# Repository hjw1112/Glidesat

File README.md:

# Glidesat
Custom devboard with additional components for ESA cansat competition. 

This PCB is for ESA cansat competition and I made it because I thought premade devboards like rp pico is too big and limiting for my team's goal. So I made this devboard to save as much space as possible and to connect to CM4 module for image processing. 

It is most complex PCB project so it was quite difficult to work on it, but with some help from background knowledge from previous projects, i think it went smoothly :)

Here are screenshots of PCB Design

## PCB Design

## Schematic

## 3D View

## Soldered PCB

---

## BOM

| Component                      |   Quantity |  Price    | Net price   | Source                                                                                    |       |    |
|:-------------------------------|-----------:|:----------|:------------|:------------------------------------------------------------------------------------------|:----------------|:-------------|
| Capacitor 1uF                  |        100 |  0.0015           |  0.15             | https://www.lcsc.com/product-detail/C14445.html                                           |              |           |
| Capacitor 0.1uF                |        100 |  0.0011           |  0.11             | https://www.lcsc.com/product-detail/C1525.html                                            |              |           |
| Capacitor 10uF                 |         50 |  0.0051           |  0.26             | https://www.lcsc.com/product-detail/C19702.html                                           |              |           |
| Capacitor 33pF                 |        100 |  0.0030           |  0.30             | https://www.lcsc.com/product-detail/C70465.html                                           |              |           |
| Capacitor 2.2nF                |        100 |  0.0033           |  0.33             | https://www.lcsc.com/product-detail/C84703.html                                           |              |           |
| B130-E3                        |         10 |  0.0435           |  0.44             | https://www.lcsc.com/product-detail/C129191.html                                          |              |           |
| LED(RED)                       |        100 |  0.0048           |  0.48             | https://www.lcsc.com/product-detail/C19171390.html                                        |              |           |
| LED(GREEN)                     |        100 |  0.0047           |  0.47             | https://www.lcsc.com/product-detail/C19273151.html                                        |              |           |
| LED(BLUE)                      |        100 |  0.0036           |  0.36             | https://www.lcsc.com/product-detail/C19171394.html                                        |              |           |
| USB_C_Receptacle_USB2.0_14P    |          5 |  0.1533           |  0.77             | https://www.lcsc.com/product-detail/C165948.html                                          |              |           |
| Header pins                    |         10 |  0.0150           |  0.15             | https://www.lcsc.com/product-detail/C42431810.html                                        |              |           |
| BM08B-GHS-TBT(LF)(SN)          |          5 |  0.3074           |  1.54             | https://www.lcsc.com/product-detail/C133062.html                                          |              |           |
| Resistor 5.1k 0603             |        100 |  0.0008           |  0.08             | https://www.lcsc.com/product-detail/C2907044.html                                         |              |           |
| Resistor 27k 0402              |        100 |  0.0006           |  0.06             | https://www.lcsc.com/product-detail/C138017.html                                          |              |           |
| Resistor 1k 0402               |        100 |  0.0006           |  0.06             | https://www.lcsc.com/product-detail/C106235.html                                          |              |           |
| Resistor 10k 0402              |        100 |  0.0006           |  0.06             | https://www.lcsc.com/product-detail/C60490.html                                           |              |           |
| Resistor 2.7k 0402             |        100 |  0.0007           |  0.07             | https://www.lcsc.com/product-detail/C138017.html                                          |              |           |
| Resistor 100k 0402             |        100 |  0.0006           |  0.06             | https://www.lcsc.com/product-detail/C60491.html                                           |              |           |
| Resistor 330 0603              |        100 |  0.0010           |  0.10             | https://www.lcsc.com/product-detail/C23138.html                                           |              |           |
| Resistor 220 0603              |        100 |  0.0010           |  0.10             | https://www.lcsc.com/product-detail/C22962.html                                           |              |           |
| Resistor 10k 0603              |        100 |  0.0010           |  0.10             | https://www.lcsc.com/product-detail/C98220.html                                           |              |           |
| Resistor 22k 0603              |        100 |  0.0011           |  0.11             | https://www.lcsc.com/product-detail/C114065.html                                          |              |           |
| SW_Push(XUNPU TS-1088-AR02016) |         10 |  0.0369           |  0.37             | https://www.lcsc.com/product-detail/C720477.html                                          |              |           |
| SW_SPST(C&K PCM12SMTR)         |          3 |  1.0445           |  3.13             | https://www.lcsc.com/product-detail/C221841.html                                          |              |           |
| MPU-6050                       |          3 |  5.9586           |  17.88             | https://www.lcsc.com/product-detail/C24112.html                                           |              |           |
| RP2040                         |          3 |  0.8250           |  2.48             | https://www.lcsc.com/product-detail/C2040.html                                            |              |           |
| AP2112K-3.3                    |          5 |  0.0803           |  0.40             | https://www.lcsc.com/product-detail/C23380830.html                                        |              |           |
| W25Q128JVSIQ                   |          3 |  1.4281           |  4.28             | https://www.lcsc.com/product-detail/C97521.html                                           |              |           |
| BMP280                         |          2 |  5.2477           |  10.50             | https://www.lcsc.com/product-detail/C83291.html                                           |              |           |
| RFM95W-868S2                   |          1 |  9.5500           |  9.55             | https://www.tme.eu/sk/en/details/rfm95cw-868s2/rf-modules/hope-microelectronics/?brutto=1 |              |           |
| X322512MSB4SI                  |         10 |  0.0592           |  0.59             | https://www.lcsc.com/product-detail/C9002.html                                            |              |           |
|                             |         |        |          |                                                                                        |              |           |
| Shipping LCSC                  |         |        |  8.49             |                                                                                        |              |           |
| Discount                       |         |        |  6.00             |                                                                                        | Component total |  64.47              |
| Shipping from time.eu          |         |        |  6.64             |                                                                                        |              |           |
|                             |         |        |          |                                                                                        |              |           |
| PCB                            |         |        |  9.70             | JLCPCB                                                                                    |              |           |
| Shipping(GSDL)                 |         |        |  7.18             |                                                                                        |              |           |
| Tax                            |         |        |  2.58             |                                                                                        | PCB Total       |  19.46              |
|                             |         |        |          |                                                                                        |              |           |
|                             |         |        |          |                                                                                        |              |           |
| TOTAL                          |         |        |  83.93EUR (about $98.82)             |                                                                                        |              |           |

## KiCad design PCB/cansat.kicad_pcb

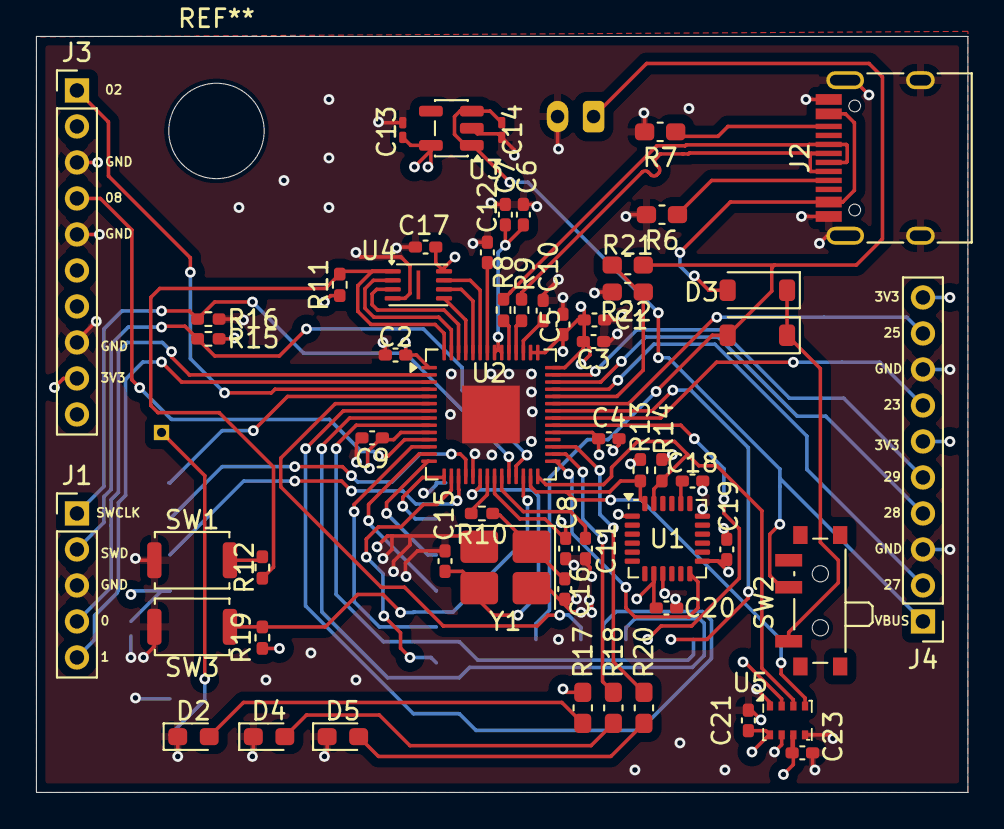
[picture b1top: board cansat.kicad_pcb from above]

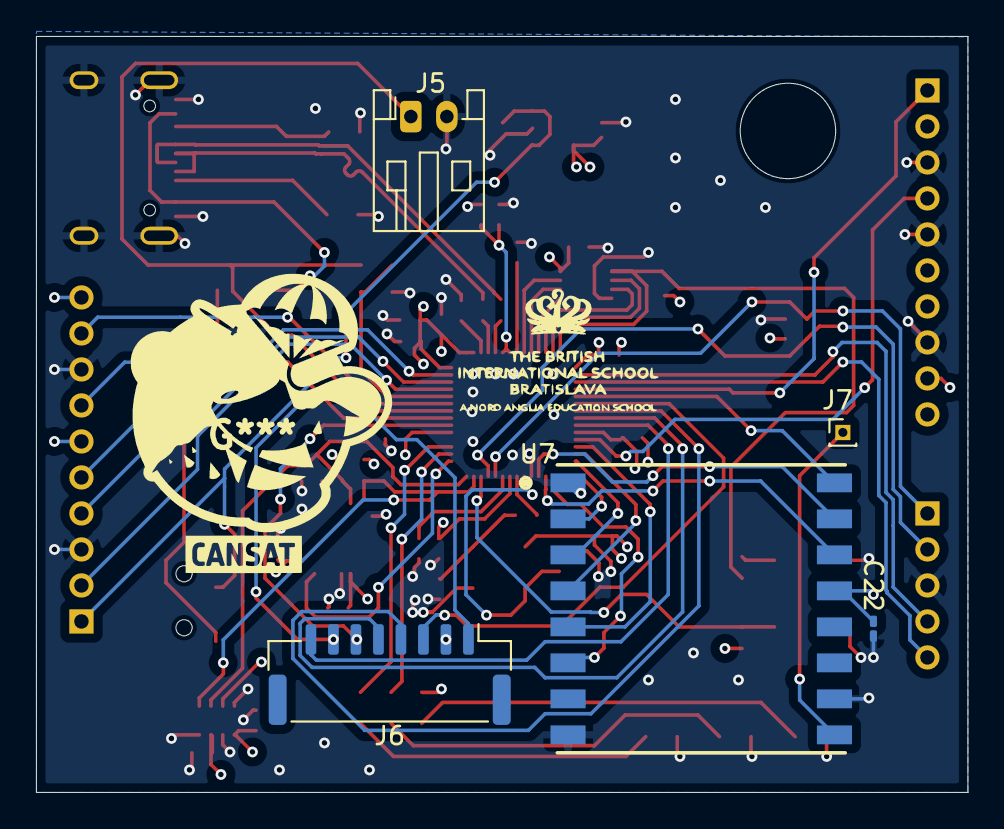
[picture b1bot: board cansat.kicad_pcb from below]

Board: 4 copper layers, 51.8 x 42.0 mm, 62 parts (5 on the bottom side), 60 nets.

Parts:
C1, C10: 1uF; C_0402_1005Metric_Pad0.74x0.62mm_HandSolder
C2, C3, C4, C5, C6, C7, C8, C9, C11, C12, C17, C19, C20, C21, C23: 0.1uF; C_0402_1005Metric_Pad0.74x0.62mm_HandSolder
C13, C14, C22: 10uF; C_0201_0603Metric_Pad0.64x0.40mm_HandSolder
C15, C16: 33pF; C_0402_1005Metric_Pad0.74x0.62mm_HandSolder
C18: 2.2nF; C_0402_1005Metric_Pad0.74x0.62mm_HandSolder
D1, D3: B130-E3; D_SOD-123
D2, D4, D5: LED; LED_0603_1608Metric_Pad1.05x0.95mm_HandSolder
J1: Debug; PinHeader_1x05_P2.00mm_Vertical
J2: USB_C_Receptacle_USB2.0_14P; USB_C_Receptacle_HRO_TYPE-C-31-M-12
J3, J4: Conn_01x10; PinHeader_1x10_P2.00mm_Vertical
J5: battery jst; JST_PH_S2B-PH-K_1x02_P2.00mm_Horizontal
J6: Conn_01x08; JST_GH_BM08B-GHS-TBT_1x08-1MP_P1.25mm_Vertical
J7: THT antenna mount point; PinHeader_1x01_P1.00mm_Vertical
R6, R7: 5.1k; C_0603_1608Metric_Pad1.08x0.95mm_HandSolder
R8, R9: 27; R_0402_1005Metric_Pad0.72x0.64mm_HandSolder
R10, R12: 1k; R_0402_1005Metric_Pad0.72x0.64mm_HandSolder
R11, R19: 10k; R_0402_1005Metric_Pad0.72x0.64mm_HandSolder
R13, R14: 2.7k; R_0402_1005Metric_Pad0.72x0.64mm_HandSolder
R15, R16: 100k; R_0402_1005Metric_Pad0.72x0.64mm_HandSolder
R17, R18, R20: 330; C_0603_1608Metric_Pad1.08x0.95mm_HandSolder
R21: 10k; C_0603_1608Metric_Pad1.08x0.95mm_HandSolder
R22: 22k; C_0603_1608Metric_Pad1.08x0.95mm_HandSolder
SW1, SW3: SW_Push; SW_Push_SPST_NO_Alps_SKRK
SW2: SW_SPST; SW_SPDT_PCM12
U1: MPU-6050; InvenSense_QFN-24_4x4mm_P0.5mm
U2: RP2040; QFN-56-1EP_7x7mm_P0.4mm_EP3.2x3.2mm
U3: AP2112K-3.3; SOT-23-5
U4: W25Q128JVS; Winbond_USON-8-1EP_3x2mm_P0.5mm_EP0.2x1.6mm
U5: BMP280; Bosch_LGA-8_2x2.5mm_P0.65mm_ClockwisePinNumbering
U7: RFM95W-868S2; XCVR_RFM95W-868S2
Y1: 12MHz; Crystal_SMD_3225-4Pin_3.2x2.5mm_HandSoldering

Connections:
+1V1: C10.1, C11.1, C12.1, U2.23 (DVDD), U2.45 (VREG_VOUT), U2.50 (DVDD)
+3V3: C1.1, C2.1, C3.1, C4.1, C5.1, C6.1, C7.1, C8.1, C9.1, C13.1, C17.1, C19.1, C20.1, C21.1, C22.2, C23.2, J3.9, J4.6, J4.10, R11.1, R13.1, R14.1, R15.1, R17.2, R19.1, U1.8 (VLOGIC), U1.13 (VDD), U2.1 (IOVDD), U2.10 (IOVDD), U2.22 (IOVDD), U2.33 (IOVDD), U2.42 (IOVDD), U2.43 (ADC_AVDD), U2.44 (VREG_IN), U2.48 (USB_VDD), U2.49 (IOVDD), U3.5 (VOUT), U4.8 (VCC), U5.2 (CSB), U5.6 (VDDIO), U5.8 (VDD), U7.13 (3.3V)
GND: C1.2, C2.2, C3.2, C4.2, C5.2, C6.2, C7.2, C8.2, C9.2, C10.2, C11.2, C12.2, C13.2, C14.2, C15.1, C16.1, C17.2, C18.2, C19.2, C20.2, C21.2, C22.1, C23.1, D2.1 (K), D4.1 (K), D5.1 (K), J1.3, J2.A1 (GND), J2.A12 (GND), J2.B1 (GND), J2.B12 (GND), J2.S1 (SHIELD), J3.3, J3.5, J3.8, J4.3, J4.8, J5.2, J6.2, R6.2, R7.2, R16.2, R22.1, SW1.1, SW3.2, U1.1 (CLKIN), U1.9 (AD0), U1.18 (GND), U2.19 (TESTEN), U2.57 (GND), U3.2 (GND), U4.4 (GND), U5.1 (GND), U5.5 (SDO), U5.7 (GND), U7.1 (GND), U7.8 (GND), U7.10 (GND), Y1.2, Y1.4
GPIO0: J1.4, U2.2 (GPIO0)
GPIO1: J1.5, U2.3 (GPIO1)
GPIO2: J3.1, U2.4 (GPIO2)
GPIO3: U2.5 (GPIO3), U7.16 (DIO2)
GPIO4: J6.3, U2.6 (GPIO4)
GPIO5: J6.4, U2.7 (GPIO5)
GPIO6: J6.5, U2.8 (GPIO6)
GPIO7: J6.8, U2.9 (GPIO7)
GPIO8: J3.4, U2.11 (GPIO8)
GPIO9: U2.12 (GPIO9), U7.5 (NSS)
GPIO10: U2.13 (GPIO10), U7.4 (SCK)
GPIO11: U2.14 (GPIO11), U7.3 (MOSI)
GPIO12: U2.15 (GPIO12), U7.2 (MISO)
GPIO13: U2.16 (GPIO13), U7.6 (RESET)
GPIO14: U2.17 (GPIO14), U7.14 (DIO0)
GPIO15: U2.18 (GPIO15), U7.15 (DIO1)
GPIO16: R13.2, U1.24 (SDA), U2.27 (GPIO16), U5.4 (SCK)
GPIO17: R14.2, U1.23 (SCL), U2.28 (GPIO17), U5.3 (SDI)
GPIO18: U1.12 (INT), U2.29 (GPIO18)
GPIO19: R18.2, U2.30 (GPIO19)
GPIO20: R20.2, U2.31 (GPIO20)
GPIO22: J6.6, U2.34 (GPIO22)
GPIO23: J4.7, U2.35 (GPIO23)
GPIO24: J6.7, U2.36 (GPIO24)
GPIO25: J4.9, U2.37 (GPIO25)
GPIO26_ADC0: R21.1, R22.2, U2.38 (GPIO26_ADC0)
GPIO27_ADC1: J4.2, U2.39 (GPIO27_ADC1)
GPIO28_ADC2: J4.4, U2.40 (GPIO28_ADC2)
GPIO29_ADC3: J4.5, U2.41 (GPIO29_ADC3)
unnamed: C16.2, R10.1, Y1.1
unnamed: D1.1 (K), D3.1 (K), SW2.1 (A)
unnamed: D2.2 (A), R17.1
unnamed: D3.2 (A), J2.A4 (VBUS), J2.A9 (VBUS), J2.B4 (VBUS), J2.B9 (VBUS)
unnamed: D4.2 (A), R18.1
unnamed: D5.2 (A), R20.1
unnamed: J2.A5 (CC1), R6.1
unnamed: J2.B5 (CC2), R7.1
unnamed: J7.1, U7.9 (ANT)
unnamed: R12.1, SW1.2
unnamed: C18.1, U1.20 (CPOUT)
unnamed: R9.2, U2.46 (USB_DM)
unnamed: R8.2, U2.47 (USB_DP)
QSPI_SCLK: U2.52 (QSPI_SCLK), U4.6 (CLK)
QSPI_SD0: U2.53 (QSPI_SD0), U4.5 (DI/IO_{0})
QSPI_SD1: U2.55 (QSPI_SD1), U4.2 (DO/IO_{1})
QSPI_SD2: U2.54 (QSPI_SD2), U4.3 (~WP/IO_{2})
QSPI_SD3: U2.51 (QSPI_SD3), U4.7 (~HOLD/~RESET/IO_{3})
QSPI_SS: R11.2, R12.2, U2.56 (QSPI_SS), U4.1 (~CS)
SWCLK: J1.1, R16.1, U2.24 (SWCLK)
SWD: J1.2, R15.2, U2.25 (SWD)
VBUS: C14.1, J4.1, SW2.2 (B), U3.1 (VIN), U3.3 (EN)
bat+: D1.2 (A), J5.1, J6.1, R21.2
run: R19.2, SW3.1, U2.26 (RUN)
usb_d+: J2.A6 (D+), J2.B6 (D+), R8.1
usb_d-: J2.A7 (D-), J2.B7 (D-), R9.1
xin: C15.2, U2.20 (XIN), Y1.3
xout: R10.2, U2.21 (XOUT)

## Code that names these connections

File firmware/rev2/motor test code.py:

# test code using micropython to verify motor circuit functionality.

import machine

en_pin = machine.Pin(10, machine.Pin.OUT)
en_pin.value(1)

led = machine.Pin(2, machine.Pin.OUT)
led.value(1)

led = machine.Pin(3, machine.Pin.OUT)
led.value(1)

"""
motor and encoder test
RP2040, DRV8838DSGR

pin map
  ph(dir)       - GPIO14
  en(pwm)       - GPIO13
  sleep         - GPIO28
  enc a         - GPIO11
  enc b         - GPIO12
"""

from machine import Pin, PWM
import time

# pin set
ph    = Pin(14, Pin.OUT)                        # dir
en    = PWM(Pin(13), freq=20_000, duty_u16=0)   # pwm
sleep = Pin(28, Pin.OUT)                        # en

enc_a = Pin(11, Pin.IN, Pin.PULL_UP)            # enc a
enc_b = Pin(12, Pin.IN, Pin.PULL_UP)            # enc b

sleep.value(1)


# encoder counter                                                     #

position = 0

def encoder_isr(pin):
    global position
    if enc_b.value():
        position += 1
    else:
        position -= 1

enc_a.irq(trigger=Pin.IRQ_RISING, handler=encoder_isr)


def motor_forward(speed):
    """speed:0-100"""
    ph.value(0)
    en.duty_u16(int(speed / 100 * 65535))

def motor_reverse(speed):
    """speed 0-100"""
    ph.value(1)
    en.duty_u16(int(speed / 100 * 65535))

def motor_brake():
    en.duty_u16(0)

def motor_coast():
    en.duty_u16(0)
    sleep.value(0)

def motor_wake():
    sleep.value(1)

# test sequence

print("=" * 40)
print("DRV8838 + encoder")
print("=" * 40)

# 1 - forward increasing speed
print("\n1. forward 25% → 100%")
position = 0
for speed in [25, 50, 75, 100]:
    motor_forward(speed)
    time.sleep(1)
    print(f"speed {speed:3d}%, encoder count: {position}")

motor_brake()
time.sleep(0.5)

# 2 - reverse increasing speed
print("\n2 reverse ramp 25% → 100%")
position = 0
for speed in [25, 50, 75, 100]:
    motor_reverse(speed)
    time.sleep(1)
    print(f"speed {speed:3d}%, encoder count: {position}")

motor_brake()
time.sleep(0.5)

# 3 - brake, coast
print("\n3 brake test")
motor_forward(75)
time.sleep(1)
motor_brake()
print("brake applied, quick stop")
time.sleep(1)

print("\n4 coast test")
motor_forward(75)
time.sleep(1)
motor_coast()
print("coasting, spin down slowly")
time.sleep(2)
motor_wake()

# 4 - encoder acc 
print("\n5 encoder accuracy - forward 3 seconds")
position = 0
motor_forward(50)
time.sleep(3)
motor_brake()
print(f"encoder count after 3s at 50%: {position} ticks")

print("\n6 - encoder accuracy — reverse 3 seconds")
position = 0
motor_reverse(50)
time.sleep(3)
motor_brake()
print(f"encoder count after 3s at 50%: {position} ticks")

# --- Done ---
print("\n" + "=" * 40)
print("complete")
print("=" * 40)
en.deinit()

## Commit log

2025-12-27 Added files
2025-12-28 BOM, Readme, images
2026-01-22 added code
2026-05-21 added all filed from new pcb(pro, source, image, review docs) and edited readme a bit.
    Journal needs to be added and readme needs to be edited for new revisions
